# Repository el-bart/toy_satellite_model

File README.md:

# toy satellite model

solar-powered toy for children.
when solar panels (PVs) are unfolded, it transmits a message configured in `main.cpp`, using [morse code](https://en.wikipedia.org/wiki/Morse_code).
currently the message is "hello humans of the planet earth". :)
message repeats as long as there is power.

PV panels are foldable.
it is possible to hold them in place with 5x5x1mm neodymium magnets.
in practice however friction-fit of a print is enough.

## rocket mount

model has been created to fit cargo bay of the [Ariane 5 model](https://github.com/el-bart/external_3d_prints/tree/master/Ariane_5).

## repo tour

repository consists of 3 main elements:
* `enc/` - 3D printable satellite enclosure (OpenSCAD).
* `sw/` - software for handling LED-blinking in morse code (C++).
* `hw/` - hardware schematic and PCB (KiCad).

all toolchains are dockerized and fully automated.
on linux machine with `docker` it is enough to type `make` in a root directory and all required things will get built for you. :)

## what's needed?

for enclosure you'll obviously need a 3D printer.
it is also possible the order the prints from a factory.
there are no special requirements or print settings
note that hinges for PVs are created using cut line segments of 1.75mm filament, rolled through PV and main body of satellite.

PCB is fairly simple.
you can either order it from your favorite PCB provider or do at home.
even though it's SMD, it deliberately uses large elements, with lots of spacing, to make hand-soldering simple.

in order to flash firmware to microcontroller you'll need a ISP programmer for ATtiny13.
[USBasp](https://www.fischl.de/usbasp/) programmer will do.
just make sure it [supports SCK to program AVR running with a slow clock](https://baszerr.eu/doku.php?id=blog:2022:08:09:2022-08-09_-_slowly_programming_slow_avrs).
note that for ATtiny13 you'll need a programming clamp, as there is no dedicated programming header.

PVs shall be glued to the surface of a PV mount with CA glue.
for the sake of usage it's highly recommended to paint the upper surface with transparent nail paint.
this will further protect panel from damages.
in case it shreds to pieces, it will also prevent small and sharp parts from landing all around the floor.

## version history

### dev
* gerber files are now generated in both `*.tar.gz` and `*.zip` formats
* added help messages for KiCad generator tools
* added BOM generator for PCB
* cable slot on PV panel changed to fit actual cable route.

### v1.1
* PCB holes for PV soldering are now using standard goldpin pitch.
* added some basic documentation.

### v1.0
* fist version even build.
* LED blinking.
* morse code supporting full alphabet.
* fully-automated build (enclosure, software and gerber files for PCB manufacturing).

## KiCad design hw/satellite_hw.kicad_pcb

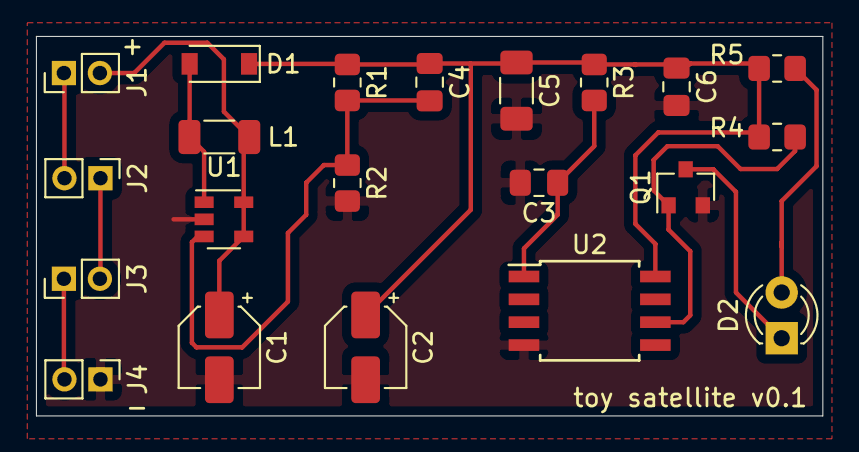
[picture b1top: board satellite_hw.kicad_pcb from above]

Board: 2 copper layers, 43.7 x 21.1 mm, 21 parts (0 on the bottom side), 12 nets.

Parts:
C1: 4.7µF; CP_Elec_4x3.9
C2: 20µF; CP_Elec_4x3.9
C3: 4.7nF; C_0805_2012Metric_Pad1.18x1.45mm_HandSolder
C4: 10pF; C_0805_2012Metric_Pad1.18x1.45mm_HandSolder
C5: 100nF; C_1206_3216Metric_Pad1.33x1.80mm_HandSolder
C6: 10nF; C_0805_2012Metric_Pad1.18x1.45mm_HandSolder
D1: D_Schottky; D_SOD-123
D2: red; LED_D3.0mm
J1: solar 1; PinHeader_1x02_P2.00mm_Vertical
J2: solar 2; PinHeader_1x02_P2.00mm_Vertical
J3: solar 3; PinHeader_1x02_P2.00mm_Vertical
J4: solar 4; PinHeader_1x02_P2.00mm_Vertical
L1: 10µH; L_1206_3216Metric_Pad1.22x1.90mm_HandSolder
Q1: 2N7002; SOT-23
R1: 680k; R_0805_2012Metric_Pad1.20x1.40mm_HandSolder
R2: 220k; R_0805_2012Metric_Pad1.20x1.40mm_HandSolder
R3, R4: 10k; R_0805_2012Metric_Pad1.20x1.40mm_HandSolder
R5: 470R; R_0805_2012Metric_Pad1.20x1.40mm_HandSolder
U1: AP3015; SOT-23-5
U2: ATtiny13-20SU; SOIJ-8_5.3x5.3mm_P1.27mm

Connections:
+5V: C2.1, C4.1, C5.1, C6.1, D1.1, R1.1, R3.1, R4.1, R5.1, U2.8
GNDD: C1.2, C2.2, C3.2, C5.2, C6.2, J4.1, Q1.2, R2.2, U1.2, U2.4
unnamed: C3.1, R3.2, U2.1
unnamed: C4.2, R1.2, R2.1, U1.3
unnamed: D1.2, L1.2, U1.1
unnamed: D2.1, Q1.3
unnamed: D2.2, R5.2
unnamed: J1.1, J2.2
unnamed: J2.1, J3.2
unnamed: J3.1, J4.2
unnamed: Q1.1, R4.2, U2.6
VCC: C1.1, J1.2, L1.1, U1.4, U1.5

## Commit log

2022-07-20 repo description
2022-07-20 empty KiCad project
2022-07-20 ignore temporary files from VIM and git
2022-07-20 added schematics for AP3015 step-up DC/DC coverter
2022-07-20 DC/DC put onto schematics
2022-07-20 updated pin negation to be better visible
2022-07-20 ingoring KiCad library backup files, too
2022-07-20 fixed values of elements to make proper DC/DC output + changed transistor for controlling LED
2022-07-20 draft of elements layout
2022-07-21 added solar panel soldering points
2022-07-21 PCB elements alignment + board ground layers
2022-07-21 removed bottom layer
2022-07-22 fixed holdpin size
2022-07-22 fixed THT LED size and pins
2022-07-22 re-arranging labels on the board
2022-07-22 ignoring generated gerber files
2022-07-22 refilled GND fill on top layer
2022-07-24 build for enclosure
2022-07-24 tools to make STL from KiCad's PCB
2022-07-24 ingoring generated elements from KiCad
2022-07-24 PCB imported
2022-07-25 KiCad model generator scripts moved to 'hw' section
2022-07-25 moved helper scripts to SDK dir
2022-07-25 SDK image name is now auto-generated for all build elements
2022-07-25 draft SDK for SW build
2022-07-25 empty patches, generated by build
2022-07-25 SDK for HW
2022-07-25 top-level makefile, for building everything in a single shot
2022-07-25 copying helper binaries to the SDK
2022-07-26 added script to generate gerber files
2022-07-26 ignoring all the build stuff
2022-07-26 added rule to generate gerber files
2022-07-26 removed redundant step of creating build dir in scirpt
2022-07-26 added more structured dir variables + deps for gerber + full md5sum output in version.txt
2022-07-26 added generation of compressed gerber archive
2022-07-26 added explicit printout for the step
2022-07-26 all zones refilled
2022-07-26 added drill file to generated gerber bundle
2022-07-26 turns out KiCad requires some config template to even start in cmdline mode
2022-07-26 added 'stl' rule to build 3D model
2022-07-26 removed comment on drill files, that are already addressed
2022-07-26 paths are now parameters
2022-07-26 added missing exit 2
2022-07-26 FreeCAD needs to have valid user entry in /etc/passwd - used fakeroot to overcome that limitation
2022-07-26 kicad2step is now less verbose
2022-07-26 added extra rule to copy pcb.stl to enclosue's build
2022-07-26 fixed path to pcb.stl (now in generated dirs, where it belongs)
2022-07-26 added main satelite body part
2022-07-26 WIP on solar panel mount
2022-07-27 added properly rounded mount for hinge in the center
2022-07-27 added cable-exit hole at the end of cable corridor
2022-08-07 schematic elements rearanged slighthly, to improve readability
2022-08-07 skeleton of the program - just blinking LED atm
2022-08-07 build + flashing routines
2022-08-07 ignoring generated content
2022-08-07 disabled fuse bits programming - there's sth off with it, and i have the very last µC on the shelve...
2022-08-07 added note on issues with slow clocks vs. programming
2022-08-07 switched default F_CPU to 9.6MHz (default for internal RC oscillator)
2022-08-09 back to 16kHz internal RC oscilator
2022-08-09 2kHz programming possible (1/8 of F_CPU=16kHz)
2022-08-09 -O3 -> -Os
2022-08-09 moved main() content into a helper class
2022-08-09 basic functions for morse code added
2022-08-09 added generic send-text helper
2022-08-09 rewored Core::run() to be templated with the text to TX
2022-08-09 Core::send_char() is now template with specializations, too
2022-08-09 removed reundant 'void'
2022-08-09 added compile-time flag to control program size, by inlining
2022-08-09 full morse code table implemented
2022-08-09 helper script to prepare text for display
2022-08-09 helper script now outputs full line
2022-08-09 helper script now splits words into lines nicely
2022-08-09 added example text: hello humans of the plannet earth
2022-08-09 switched for inlining, as it resulted in smaller program, for a given text
2022-08-09 removed unnecessary inlines from *_pause() helper functions
2022-08-09 added missing set of AVR lirbaries to the build
2022-08-09 added 3-clause BSD as a license
2022-08-17 decreased height of side-foot panel holder
2022-08-17 properly aligned magnets on PV panels holders + magnets on bottom of main satelite body
2022-08-17 removed hardcode from pv_panel_mount() centering routine
2022-08-17 moved whole structure to the center of coordinates
2022-08-17 added more space for PV mount and mount block, so that it can roll easier on the final setup
2022-08-17 added side pv_harness(), consisting of 2 blocks
2022-08-17 added 4x PV panels harnesses + visualization
2022-08-17 moved PCB mock to main_block()'s interior
2022-08-17 PCB moved a bit aside
2022-08-17 TODOs added
2022-08-17 added top_cap() model
2022-08-17 moved config to a separate file
2022-08-17 top_cap() moved to a seprate file
2022-08-17 PV panel moved to a separate file
2022-08-17 added 4x panels for printing
2022-08-17 added cable holes for PV panels
2022-08-19 removed outdated TODO
2022-08-19 added model of a rocket_mount()
2022-08-19 added rocket_mount() to main model + fixed formatting in one place + removed solved TODO
2022-08-19 minimized size of rocket_mount()'s base, to make sure it fits into the Ariane 5 model's cargo bay
2022-08-20 fixed pinheaders to math with typical goldpins
2022-08-20 ignoring kwrite's temp files
2022-08-20 fixed typo in the message
2022-08-20 basic project documentation + some photos
2022-08-22 fixed cable routing
2022-08-22 removed unused file
2022-08-22 added BOM generator for PCB
2022-08-22 integrated BOM generatio into main HW build
2022-08-22 added help to all KiCad generators
2022-08-22 added to readme info about KiCad generator tools help
2022-08-26 greber files are now generated in both *.zip and *.tar.gz format
2022-08-27 fixed gerber files creation for both tar and zip
